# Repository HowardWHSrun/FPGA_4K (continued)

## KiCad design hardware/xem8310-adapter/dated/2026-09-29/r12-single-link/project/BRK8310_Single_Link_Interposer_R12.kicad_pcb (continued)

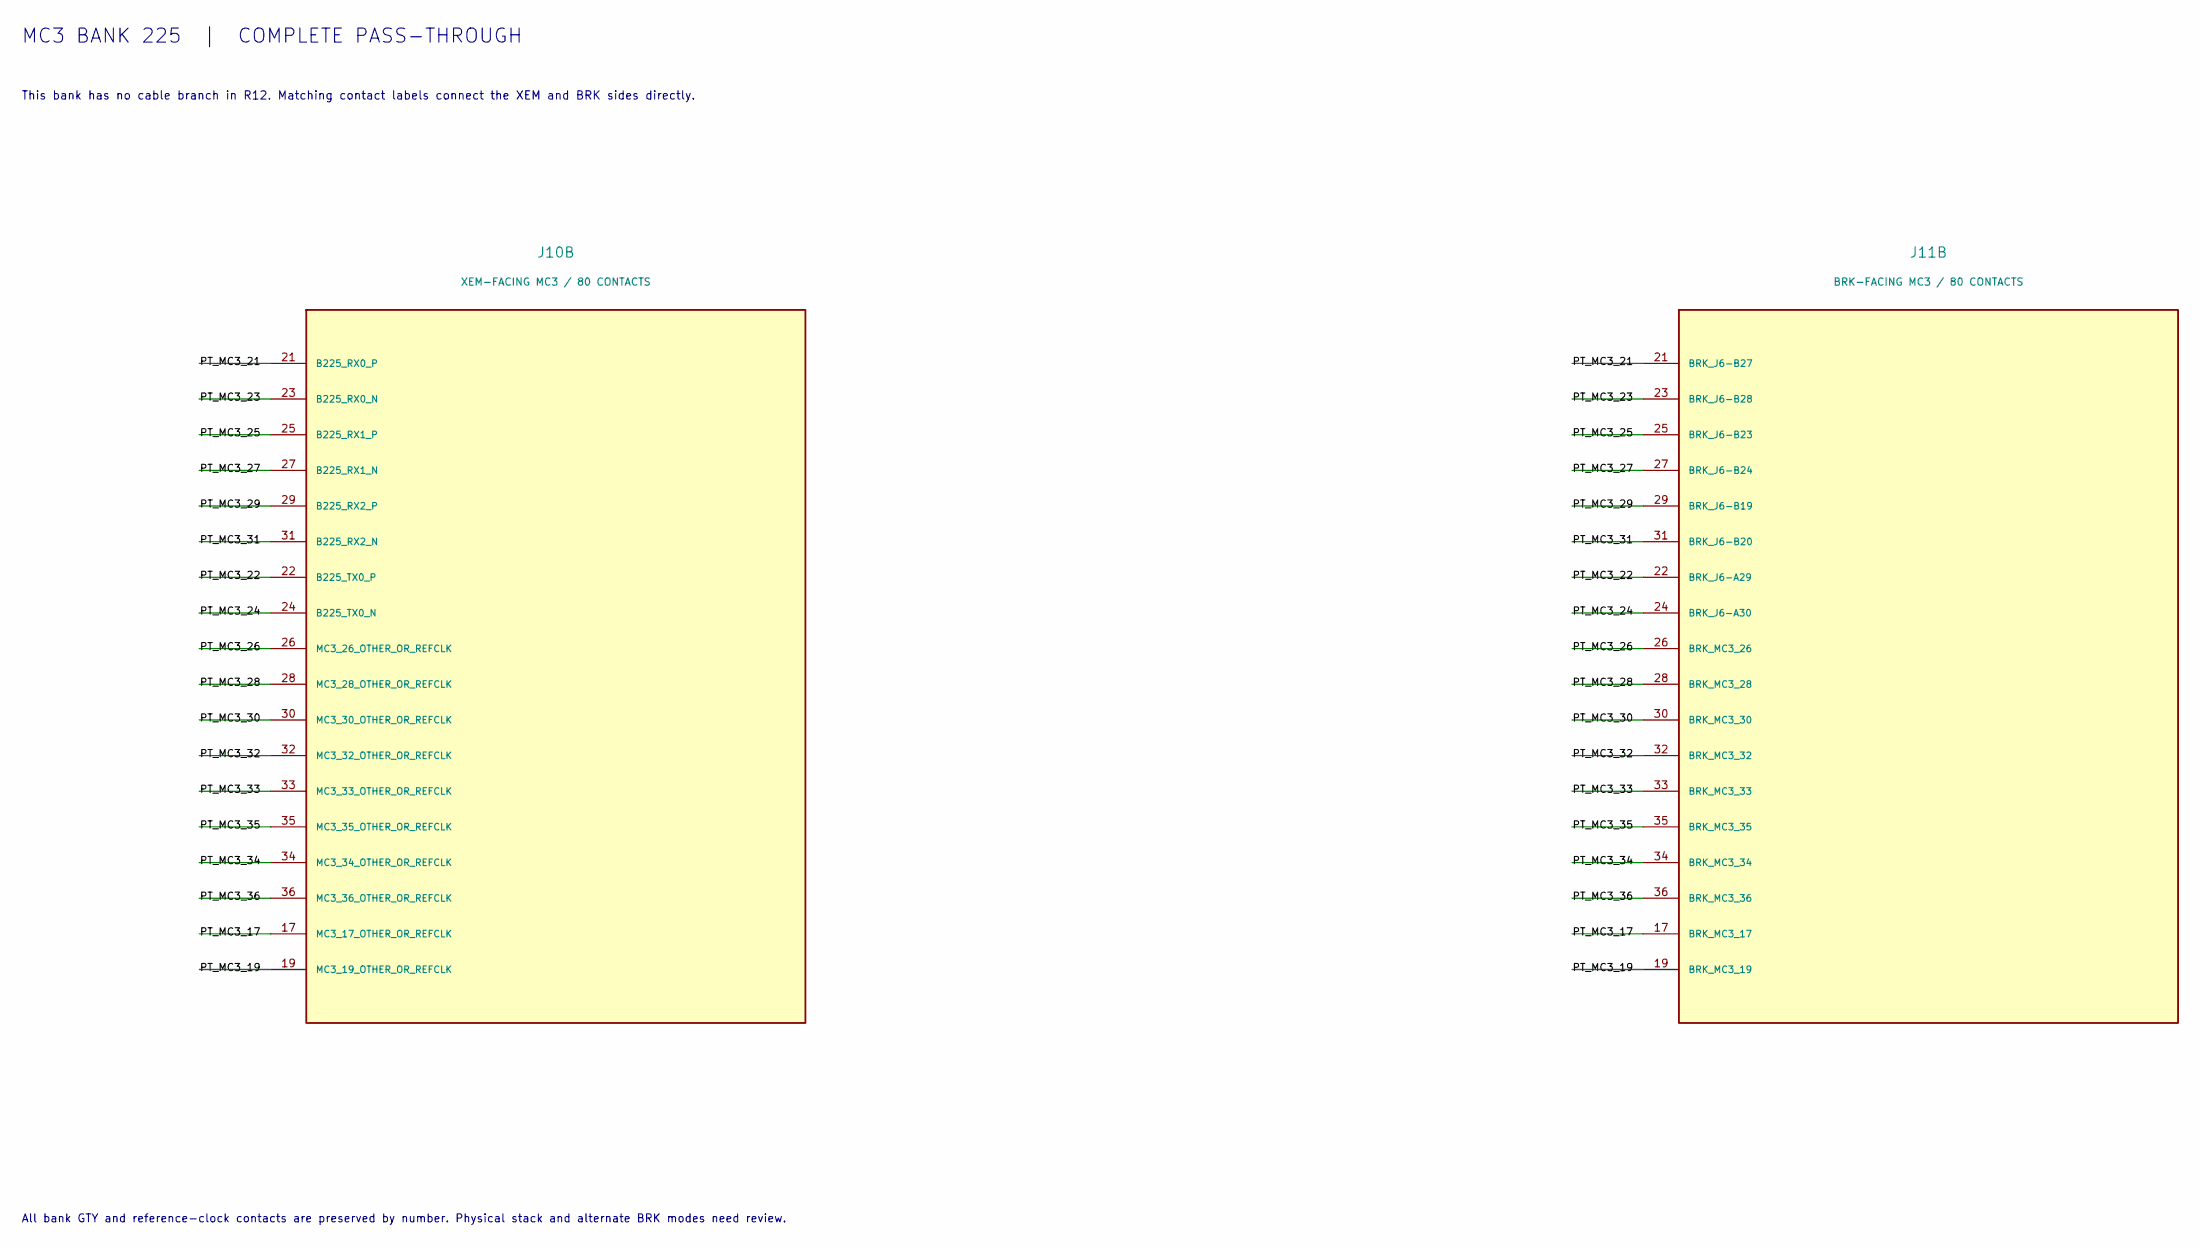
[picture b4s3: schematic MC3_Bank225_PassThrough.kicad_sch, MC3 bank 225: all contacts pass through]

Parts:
J10: XEM-FACING MC3 / 80 CONTACTS; QTH_040_01_Top_OpalKelly
J11: BRK-FACING MC3 / 80 CONTACTS; QSH_040_01_Bottom_SamtecDrawing

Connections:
/03 / MC3 BANK 225 - COMPLETE PASS-THROUGH/PT_MC3_17: J10.17 (MC3_17_OTHER_OR_REFCLK), J11.17 (BRK_MC3_17)
/03 / MC3 BANK 225 - COMPLETE PASS-THROUGH/PT_MC3_19: J10.19 (MC3_19_OTHER_OR_REFCLK), J11.19 (BRK_MC3_19)
/03 / MC3 BANK 225 - COMPLETE PASS-THROUGH/PT_MC3_21: J10.21 (B225_RX0_P), J11.21 (BRK_J6-B27)
/03 / MC3 BANK 225 - COMPLETE PASS-THROUGH/PT_MC3_22: J10.22 (B225_TX0_P), J11.22 (BRK_J6-A29)
/03 / MC3 BANK 225 - COMPLETE PASS-THROUGH/PT_MC3_23: J10.23 (B225_RX0_N), J11.23 (BRK_J6-B28)
/03 / MC3 BANK 225 - COMPLETE PASS-THROUGH/PT_MC3_24: J10.24 (B225_TX0_N), J11.24 (BRK_J6-A30)
/03 / MC3 BANK 225 - COMPLETE PASS-THROUGH/PT_MC3_25: J10.25 (B225_RX1_P), J11.25 (BRK_J6-B23)
/03 / MC3 BANK 225 - COMPLETE PASS-THROUGH/PT_MC3_26: J10.26 (MC3_26_OTHER_OR_REFCLK), J11.26 (BRK_MC3_26)
/03 / MC3 BANK 225 - COMPLETE PASS-THROUGH/PT_MC3_27: J10.27 (B225_RX1_N), J11.27 (BRK_J6-B24)
/03 / MC3 BANK 225 - COMPLETE PASS-THROUGH/PT_MC3_28: J10.28 (MC3_28_OTHER_OR_REFCLK), J11.28 (BRK_MC3_28)
/03 / MC3 BANK 225 - COMPLETE PASS-THROUGH/PT_MC3_29: J10.29 (B225_RX2_P), J11.29 (BRK_J6-B19)
/03 / MC3 BANK 225 - COMPLETE PASS-THROUGH/PT_MC3_30: J10.30 (MC3_30_OTHER_OR_REFCLK), J11.30 (BRK_MC3_30)
/03 / MC3 BANK 225 - COMPLETE PASS-THROUGH/PT_MC3_31: J10.31 (B225_RX2_N), J11.31 (BRK_J6-B20)
/03 / MC3 BANK 225 - COMPLETE PASS-THROUGH/PT_MC3_32: J10.32 (MC3_32_OTHER_OR_REFCLK), J11.32 (BRK_MC3_32)
/03 / MC3 BANK 225 - COMPLETE PASS-THROUGH/PT_MC3_33: J10.33 (MC3_33_OTHER_OR_REFCLK), J11.33 (BRK_MC3_33)
/03 / MC3 BANK 225 - COMPLETE PASS-THROUGH/PT_MC3_34: J10.34 (MC3_34_OTHER_OR_REFCLK), J11.34 (BRK_MC3_34)
/03 / MC3 BANK 225 - COMPLETE PASS-THROUGH/PT_MC3_35: J10.35 (MC3_35_OTHER_OR_REFCLK), J11.35 (BRK_MC3_35)
/03 / MC3 BANK 225 - COMPLETE PASS-THROUGH/PT_MC3_36: J10.36 (MC3_36_OTHER_OR_REFCLK), J11.36 (BRK_MC3_36)

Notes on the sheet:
MC3 BANK 225 | COMPLETE PASS-THROUGH
This bank has no cable branch in R12. Matching contact labels connect the XEM and BRK sides directly.
All bank GTY and reference-clock contacts are preserved by number. Physical stack and alternate BRK modes need review.

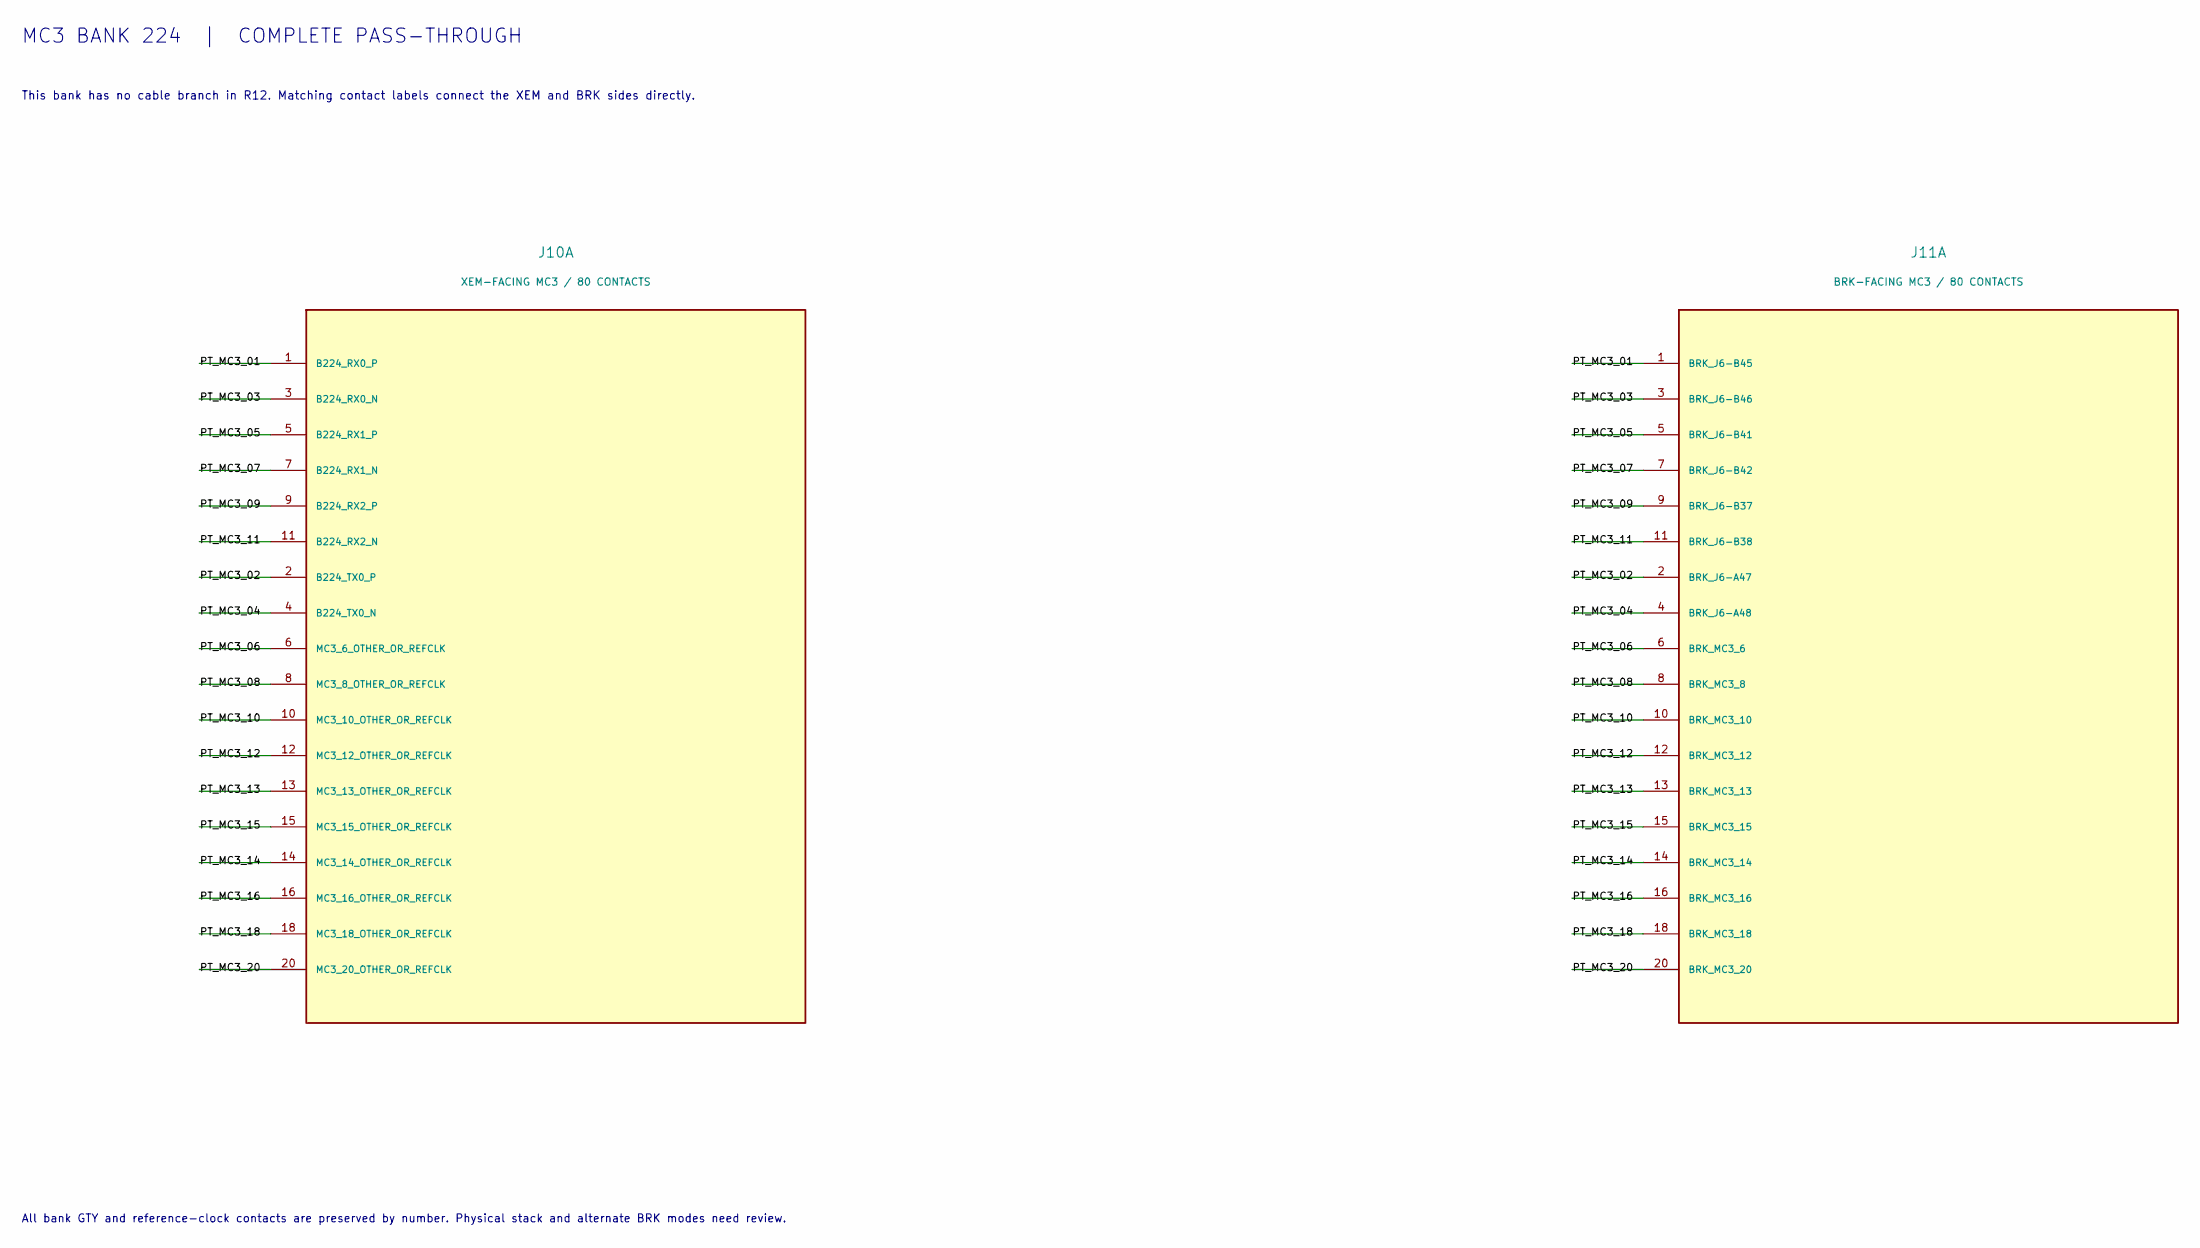
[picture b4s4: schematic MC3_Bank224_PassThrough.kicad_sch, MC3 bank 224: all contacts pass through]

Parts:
J10: XEM-FACING MC3 / 80 CONTACTS; QTH_040_01_Top_OpalKelly
J11: BRK-FACING MC3 / 80 CONTACTS; QSH_040_01_Bottom_SamtecDrawing

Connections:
/04 / MC3 BANK 224 - COMPLETE PASS-THROUGH/PT_MC3_01: J10.1 (B224_RX0_P), J11.1 (BRK_J6-B45)
/04 / MC3 BANK 224 - COMPLETE PASS-THROUGH/PT_MC3_02: J10.2 (B224_TX0_P), J11.2 (BRK_J6-A47)
/04 / MC3 BANK 224 - COMPLETE PASS-THROUGH/PT_MC3_03: J10.3 (B224_RX0_N), J11.3 (BRK_J6-B46)
/04 / MC3 BANK 224 - COMPLETE PASS-THROUGH/PT_MC3_04: J10.4 (B224_TX0_N), J11.4 (BRK_J6-A48)
/04 / MC3 BANK 224 - COMPLETE PASS-THROUGH/PT_MC3_05: J10.5 (B224_RX1_P), J11.5 (BRK_J6-B41)
/04 / MC3 BANK 224 - COMPLETE PASS-THROUGH/PT_MC3_06: J10.6 (MC3_6_OTHER_OR_REFCLK), J11.6 (BRK_MC3_6)
/04 / MC3 BANK 224 - COMPLETE PASS-THROUGH/PT_MC3_07: J10.7 (B224_RX1_N), J11.7 (BRK_J6-B42)
/04 / MC3 BANK 224 - COMPLETE PASS-THROUGH/PT_MC3_08: J10.8 (MC3_8_OTHER_OR_REFCLK), J11.8 (BRK_MC3_8)
/04 / MC3 BANK 224 - COMPLETE PASS-THROUGH/PT_MC3_09: J10.9 (B224_RX2_P), J11.9 (BRK_J6-B37)
/04 / MC3 BANK 224 - COMPLETE PASS-THROUGH/PT_MC3_10: J10.10 (MC3_10_OTHER_OR_REFCLK), J11.10 (BRK_MC3_10)
/04 / MC3 BANK 224 - COMPLETE PASS-THROUGH/PT_MC3_11: J10.11 (B224_RX2_N), J11.11 (BRK_J6-B38)
/04 / MC3 BANK 224 - COMPLETE PASS-THROUGH/PT_MC3_12: J10.12 (MC3_12_OTHER_OR_REFCLK), J11.12 (BRK_MC3_12)
/04 / MC3 BANK 224 - COMPLETE PASS-THROUGH/PT_MC3_13: J10.13 (MC3_13_OTHER_OR_REFCLK), J11.13 (BRK_MC3_13)
/04 / MC3 BANK 224 - COMPLETE PASS-THROUGH/PT_MC3_14: J10.14 (MC3_14_OTHER_OR_REFCLK), J11.14 (BRK_MC3_14)
/04 / MC3 BANK 224 - COMPLETE PASS-THROUGH/PT_MC3_15: J10.15 (MC3_15_OTHER_OR_REFCLK), J11.15 (BRK_MC3_15)
/04 / MC3 BANK 224 - COMPLETE PASS-THROUGH/PT_MC3_16: J10.16 (MC3_16_OTHER_OR_REFCLK), J11.16 (BRK_MC3_16)
/04 / MC3 BANK 224 - COMPLETE PASS-THROUGH/PT_MC3_18: J10.18 (MC3_18_OTHER_OR_REFCLK), J11.18 (BRK_MC3_18)
/04 / MC3 BANK 224 - COMPLETE PASS-THROUGH/PT_MC3_20: J10.20 (MC3_20_OTHER_OR_REFCLK), J11.20 (BRK_MC3_20)

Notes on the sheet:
MC3 BANK 224 | COMPLETE PASS-THROUGH
This bank has no cable branch in R12. Matching contact labels connect the XEM and BRK sides directly.
All bank GTY and reference-clock contacts are preserved by number. Physical stack and alternate BRK modes need review.

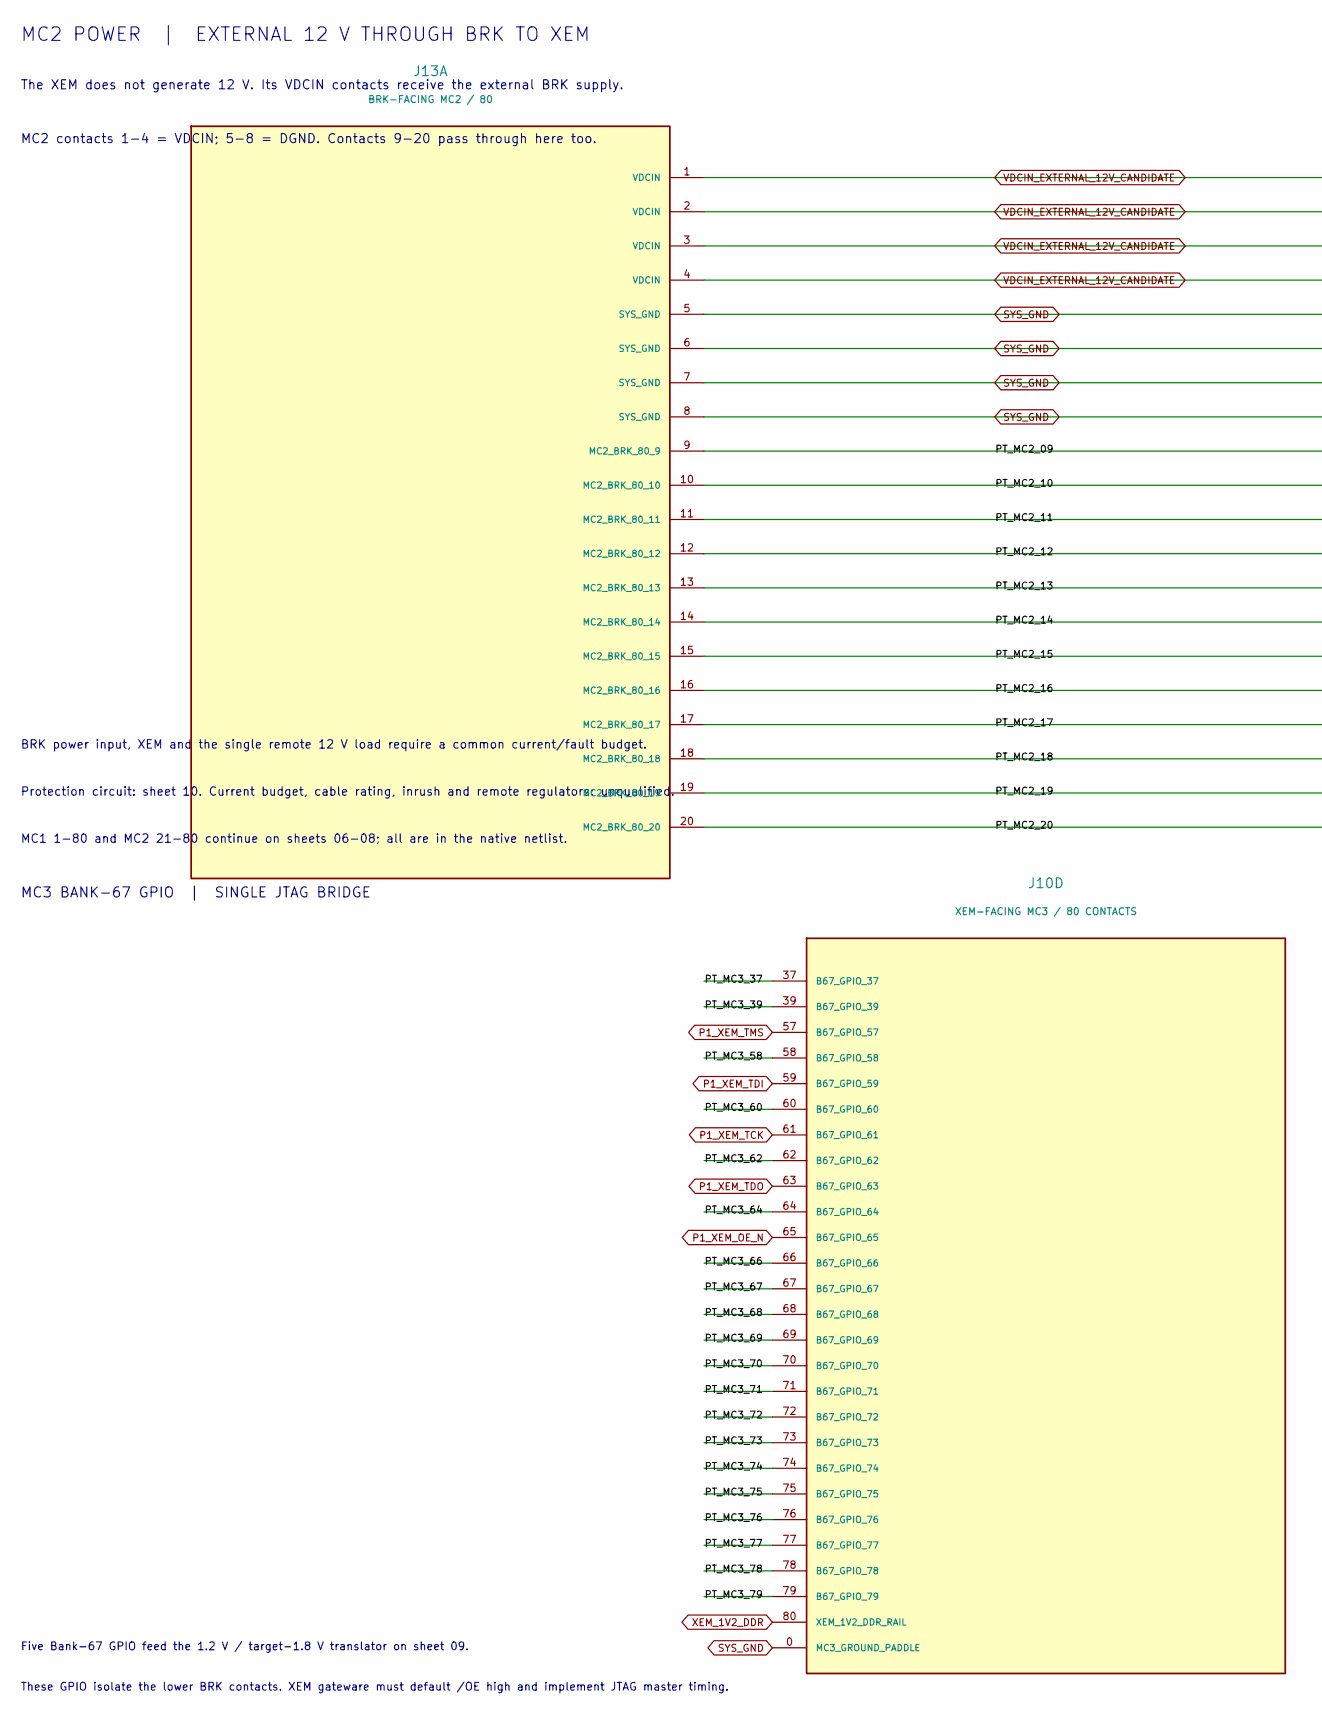
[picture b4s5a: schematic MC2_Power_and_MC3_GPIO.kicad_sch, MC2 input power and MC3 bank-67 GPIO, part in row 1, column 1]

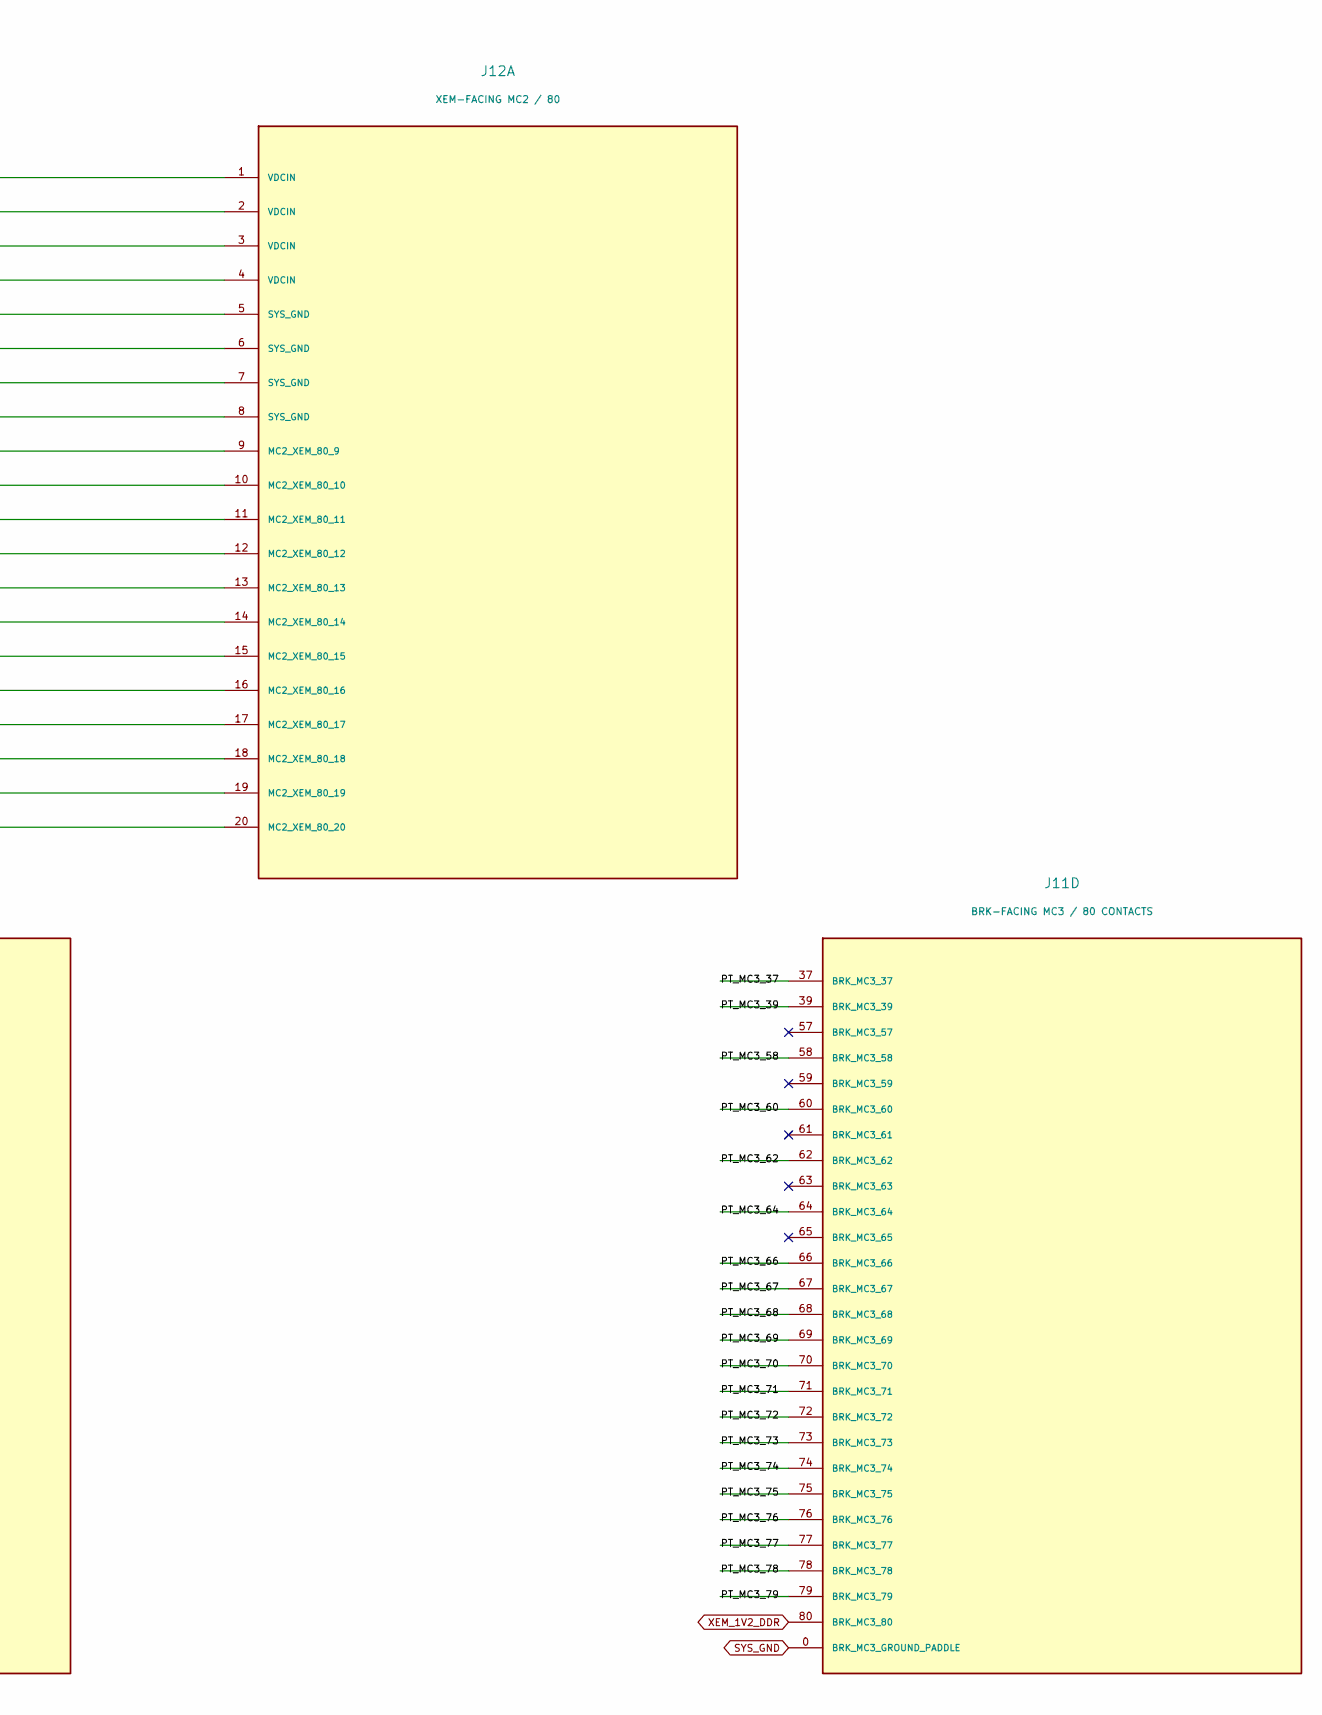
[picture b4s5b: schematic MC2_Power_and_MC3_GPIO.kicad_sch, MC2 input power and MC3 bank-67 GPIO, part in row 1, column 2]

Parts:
J10: XEM-FACING MC3 / 80 CONTACTS; QTH_040_01_Top_OpalKelly
J11: BRK-FACING MC3 / 80 CONTACTS; QSH_040_01_Bottom_SamtecDrawing
J12: XEM-FACING MC2 / 80; BTE_040_01_Top_OpalKelly
J13: BRK-FACING MC2 / 80; BSE_040_01_Bottom_SamtecDrawing

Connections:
/05 / MC2 POWER + MC3 BANK-67 GPIO/PT_MC2_09: J12.9 (MC2_XEM_80_9), J13.9 (MC2_BRK_80_9)
/05 / MC2 POWER + MC3 BANK-67 GPIO/PT_MC2_10: J12.10 (MC2_XEM_80_10), J13.10 (MC2_BRK_80_10)
/05 / MC2 POWER + MC3 BANK-67 GPIO/PT_MC2_11: J12.11 (MC2_XEM_80_11), J13.11 (MC2_BRK_80_11)
/05 / MC2 POWER + MC3 BANK-67 GPIO/PT_MC2_12: J12.12 (MC2_XEM_80_12), J13.12 (MC2_BRK_80_12)
/05 / MC2 POWER + MC3 BANK-67 GPIO/PT_MC2_13: J12.13 (MC2_XEM_80_13), J13.13 (MC2_BRK_80_13)
/05 / MC2 POWER + MC3 BANK-67 GPIO/PT_MC2_14: J12.14 (MC2_XEM_80_14), J13.14 (MC2_BRK_80_14)
/05 / MC2 POWER + MC3 BANK-67 GPIO/PT_MC2_15: J12.15 (MC2_XEM_80_15), J13.15 (MC2_BRK_80_15)
/05 / MC2 POWER + MC3 BANK-67 GPIO/PT_MC2_16: J12.16 (MC2_XEM_80_16), J13.16 (MC2_BRK_80_16)
/05 / MC2 POWER + MC3 BANK-67 GPIO/PT_MC2_17: J12.17 (MC2_XEM_80_17), J13.17 (MC2_BRK_80_17)
/05 / MC2 POWER + MC3 BANK-67 GPIO/PT_MC2_18: J12.18 (MC2_XEM_80_18), J13.18 (MC2_BRK_80_18)
/05 / MC2 POWER + MC3 BANK-67 GPIO/PT_MC2_19: J12.19 (MC2_XEM_80_19), J13.19 (MC2_BRK_80_19)
/05 / MC2 POWER + MC3 BANK-67 GPIO/PT_MC2_20: J12.20 (MC2_XEM_80_20), J13.20 (MC2_BRK_80_20)
/05 / MC2 POWER + MC3 BANK-67 GPIO/PT_MC3_37: J10.37 (B67_GPIO_37), J11.37 (BRK_MC3_37)
/05 / MC2 POWER + MC3 BANK-67 GPIO/PT_MC3_39: J10.39 (B67_GPIO_39), J11.39 (BRK_MC3_39)
/05 / MC2 POWER + MC3 BANK-67 GPIO/PT_MC3_58: J10.58 (B67_GPIO_58), J11.58 (BRK_MC3_58)
/05 / MC2 POWER + MC3 BANK-67 GPIO/PT_MC3_60: J10.60 (B67_GPIO_60), J11.60 (BRK_MC3_60)
/05 / MC2 POWER + MC3 BANK-67 GPIO/PT_MC3_62: J10.62 (B67_GPIO_62), J11.62 (BRK_MC3_62)
/05 / MC2 POWER + MC3 BANK-67 GPIO/PT_MC3_64: J10.64 (B67_GPIO_64), J11.64 (BRK_MC3_64)
/05 / MC2 POWER + MC3 BANK-67 GPIO/PT_MC3_66: J10.66 (B67_GPIO_66), J11.66 (BRK_MC3_66)
/05 / MC2 POWER + MC3 BANK-67 GPIO/PT_MC3_67: J10.67 (B67_GPIO_67), J11.67 (BRK_MC3_67)
/05 / MC2 POWER + MC3 BANK-67 GPIO/PT_MC3_68: J10.68 (B67_GPIO_68), J11.68 (BRK_MC3_68)
/05 / MC2 POWER + MC3 BANK-67 GPIO/PT_MC3_69: J10.69 (B67_GPIO_69), J11.69 (BRK_MC3_69)
/05 / MC2 POWER + MC3 BANK-67 GPIO/PT_MC3_70: J10.70 (B67_GPIO_70), J11.70 (BRK_MC3_70)
/05 / MC2 POWER + MC3 BANK-67 GPIO/PT_MC3_71: J10.71 (B67_GPIO_71), J11.71 (BRK_MC3_71)
/05 / MC2 POWER + MC3 BANK-67 GPIO/PT_MC3_72: J10.72 (B67_GPIO_72), J11.72 (BRK_MC3_72)
/05 / MC2 POWER + MC3 BANK-67 GPIO/PT_MC3_73: J10.73 (B67_GPIO_73), J11.73 (BRK_MC3_73)
/05 / MC2 POWER + MC3 BANK-67 GPIO/PT_MC3_74: J10.74 (B67_GPIO_74), J11.74 (BRK_MC3_74)
/05 / MC2 POWER + MC3 BANK-67 GPIO/PT_MC3_75: J10.75 (B67_GPIO_75), J11.75 (BRK_MC3_75)
/05 / MC2 POWER + MC3 BANK-67 GPIO/PT_MC3_76: J10.76 (B67_GPIO_76), J11.76 (BRK_MC3_76)
/05 / MC2 POWER + MC3 BANK-67 GPIO/PT_MC3_77: J10.77 (B67_GPIO_77), J11.77 (BRK_MC3_77)
/05 / MC2 POWER + MC3 BANK-67 GPIO/PT_MC3_78: J10.78 (B67_GPIO_78), J11.78 (BRK_MC3_78)
/05 / MC2 POWER + MC3 BANK-67 GPIO/PT_MC3_79: J10.79 (B67_GPIO_79), J11.79 (BRK_MC3_79)
P1_XEM_OE_N: J10.65 (B67_GPIO_65); also elsewhere on the board
P1_XEM_TCK: J10.61 (B67_GPIO_61); also elsewhere on the board
P1_XEM_TDI: J10.59 (B67_GPIO_59); also elsewhere on the board
P1_XEM_TDO: J10.63 (B67_GPIO_63); also elsewhere on the board
P1_XEM_TMS: J10.57 (B67_GPIO_57); also elsewhere on the board
SYS_GND: J10.0 (MC3_GROUND_PADDLE), J11.0 (BRK_MC3_GROUND_PADDLE), J12.5 (SYS_GND), J12.6 (SYS_GND), J12.7 (SYS_GND), J12.8 (SYS_GND), J13.5 (SYS_GND), J13.6 (SYS_GND), J13.7 (SYS_GND), J13.8 (SYS_GND); also elsewhere on the board
VDCIN_EXTERNAL_12V_CANDIDATE: J12.1 (VDCIN), J12.2 (VDCIN), J12.3 (VDCIN), J12.4 (VDCIN), J13.1 (VDCIN), J13.2 (VDCIN), J13.3 (VDCIN), J13.4 (VDCIN); also elsewhere on the board
XEM_1V2_DDR: J10.80 (XEM_1V2_DDR_RAIL), J11.80 (BRK_MC3_80); also elsewhere on the board

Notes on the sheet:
MC2 POWER | EXTERNAL 12 V THROUGH BRK TO XEM
The XEM does not generate 12 V. Its VDCIN contacts receive the external BRK supply.
MC2 contacts 1-4 = VDCIN; 5-8 = DGND. Contacts 9-20 pass through here too.
BRK power input, XEM and the single remote 12 V load require a common current/fault budget.
Protection circuit: sheet 10. Current budget, cable rating, inrush and remote regulators: unqualified.
MC1 1-80 and MC2 21-80 continue on sheets 06-08; all are in the native netlist.
MC3 BANK-67 GPIO | SINGLE JTAG BRIDGE
Five Bank-67 GPIO feed the 1.2 V / target-1.8 V translator on sheet 09.
These GPIO isolate the lower BRK contacts. XEM gateware must default /OE high and implement JTAG master timing.

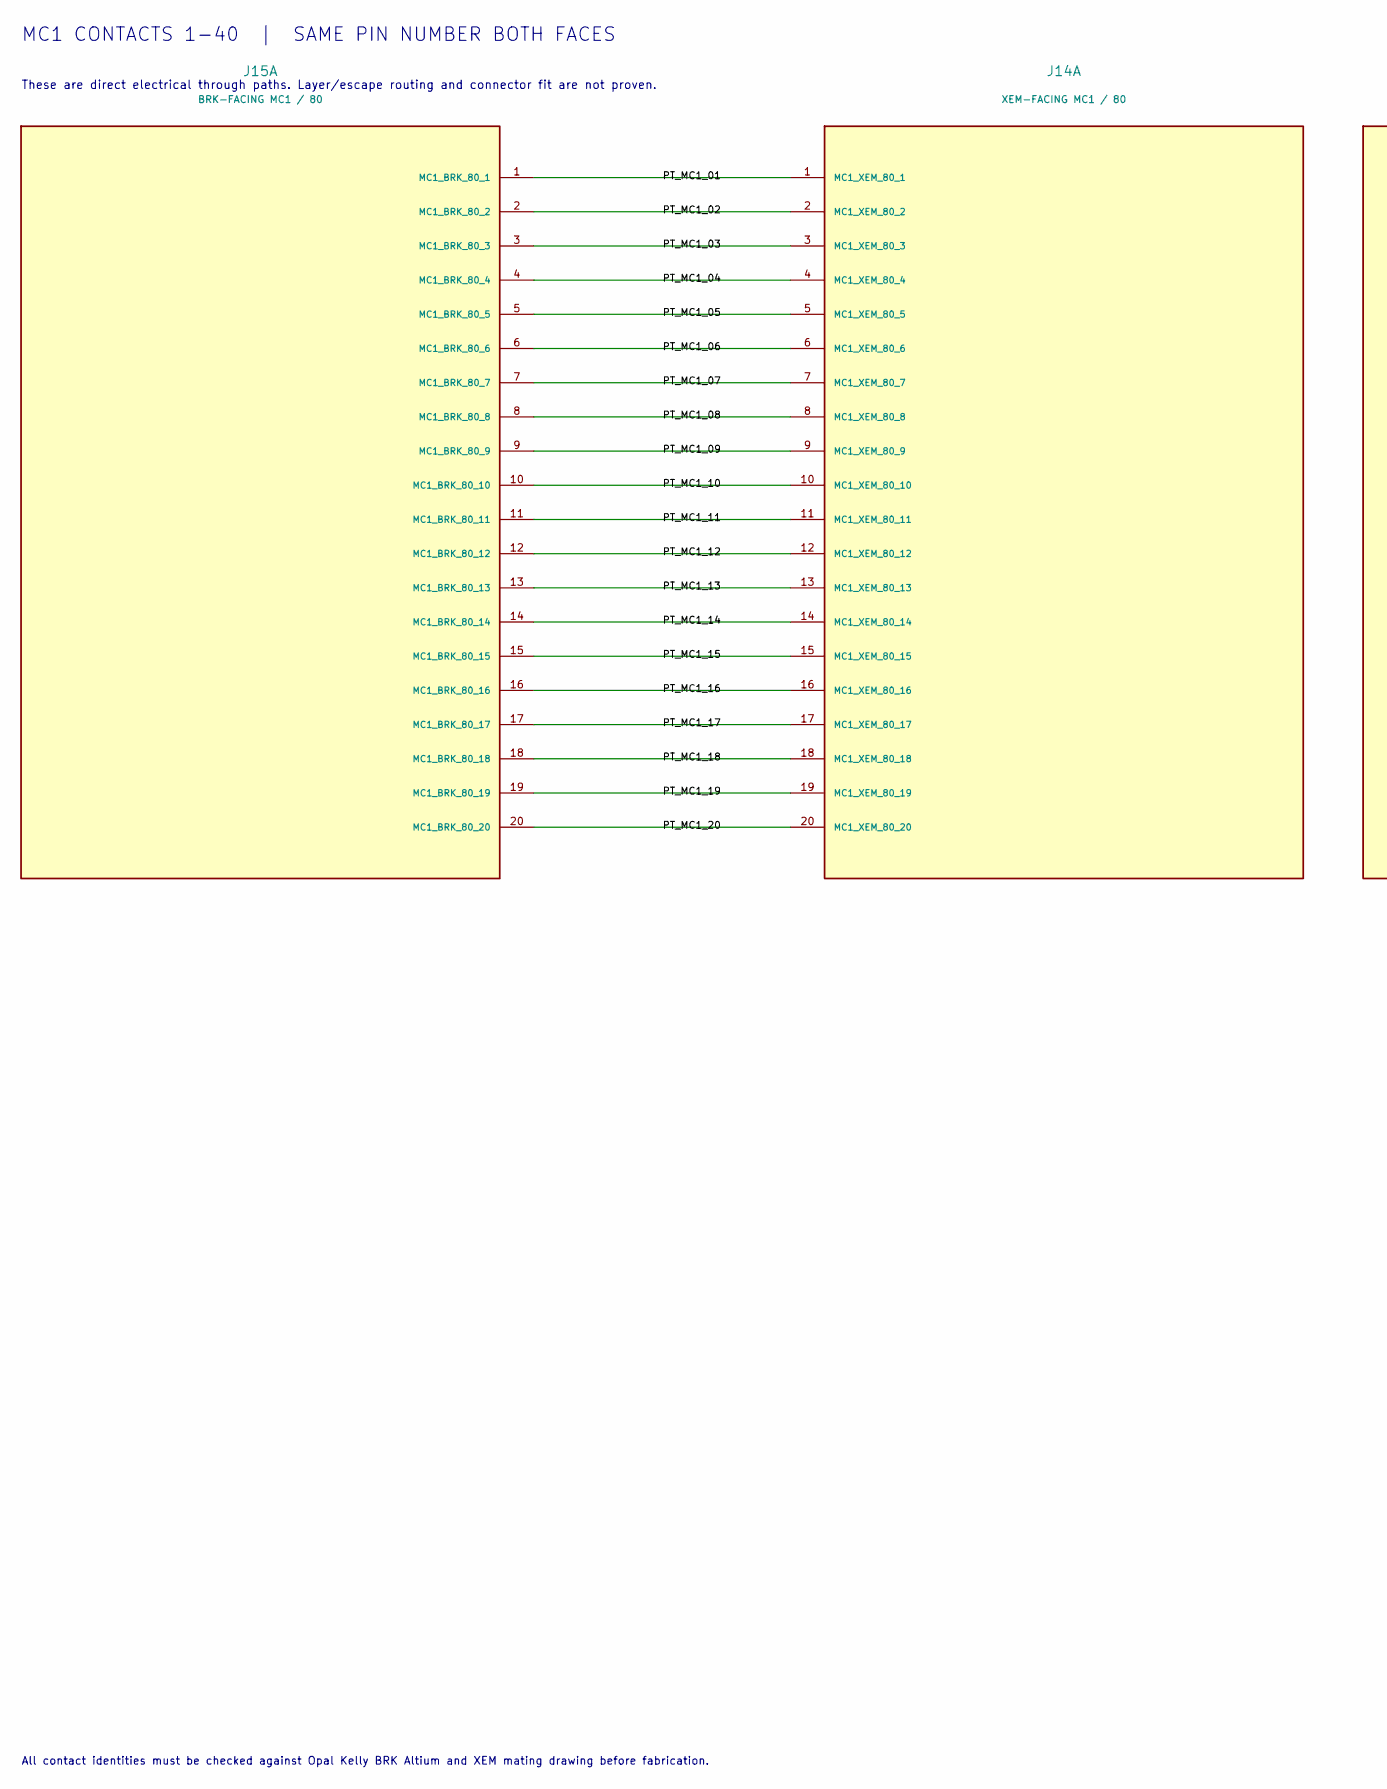
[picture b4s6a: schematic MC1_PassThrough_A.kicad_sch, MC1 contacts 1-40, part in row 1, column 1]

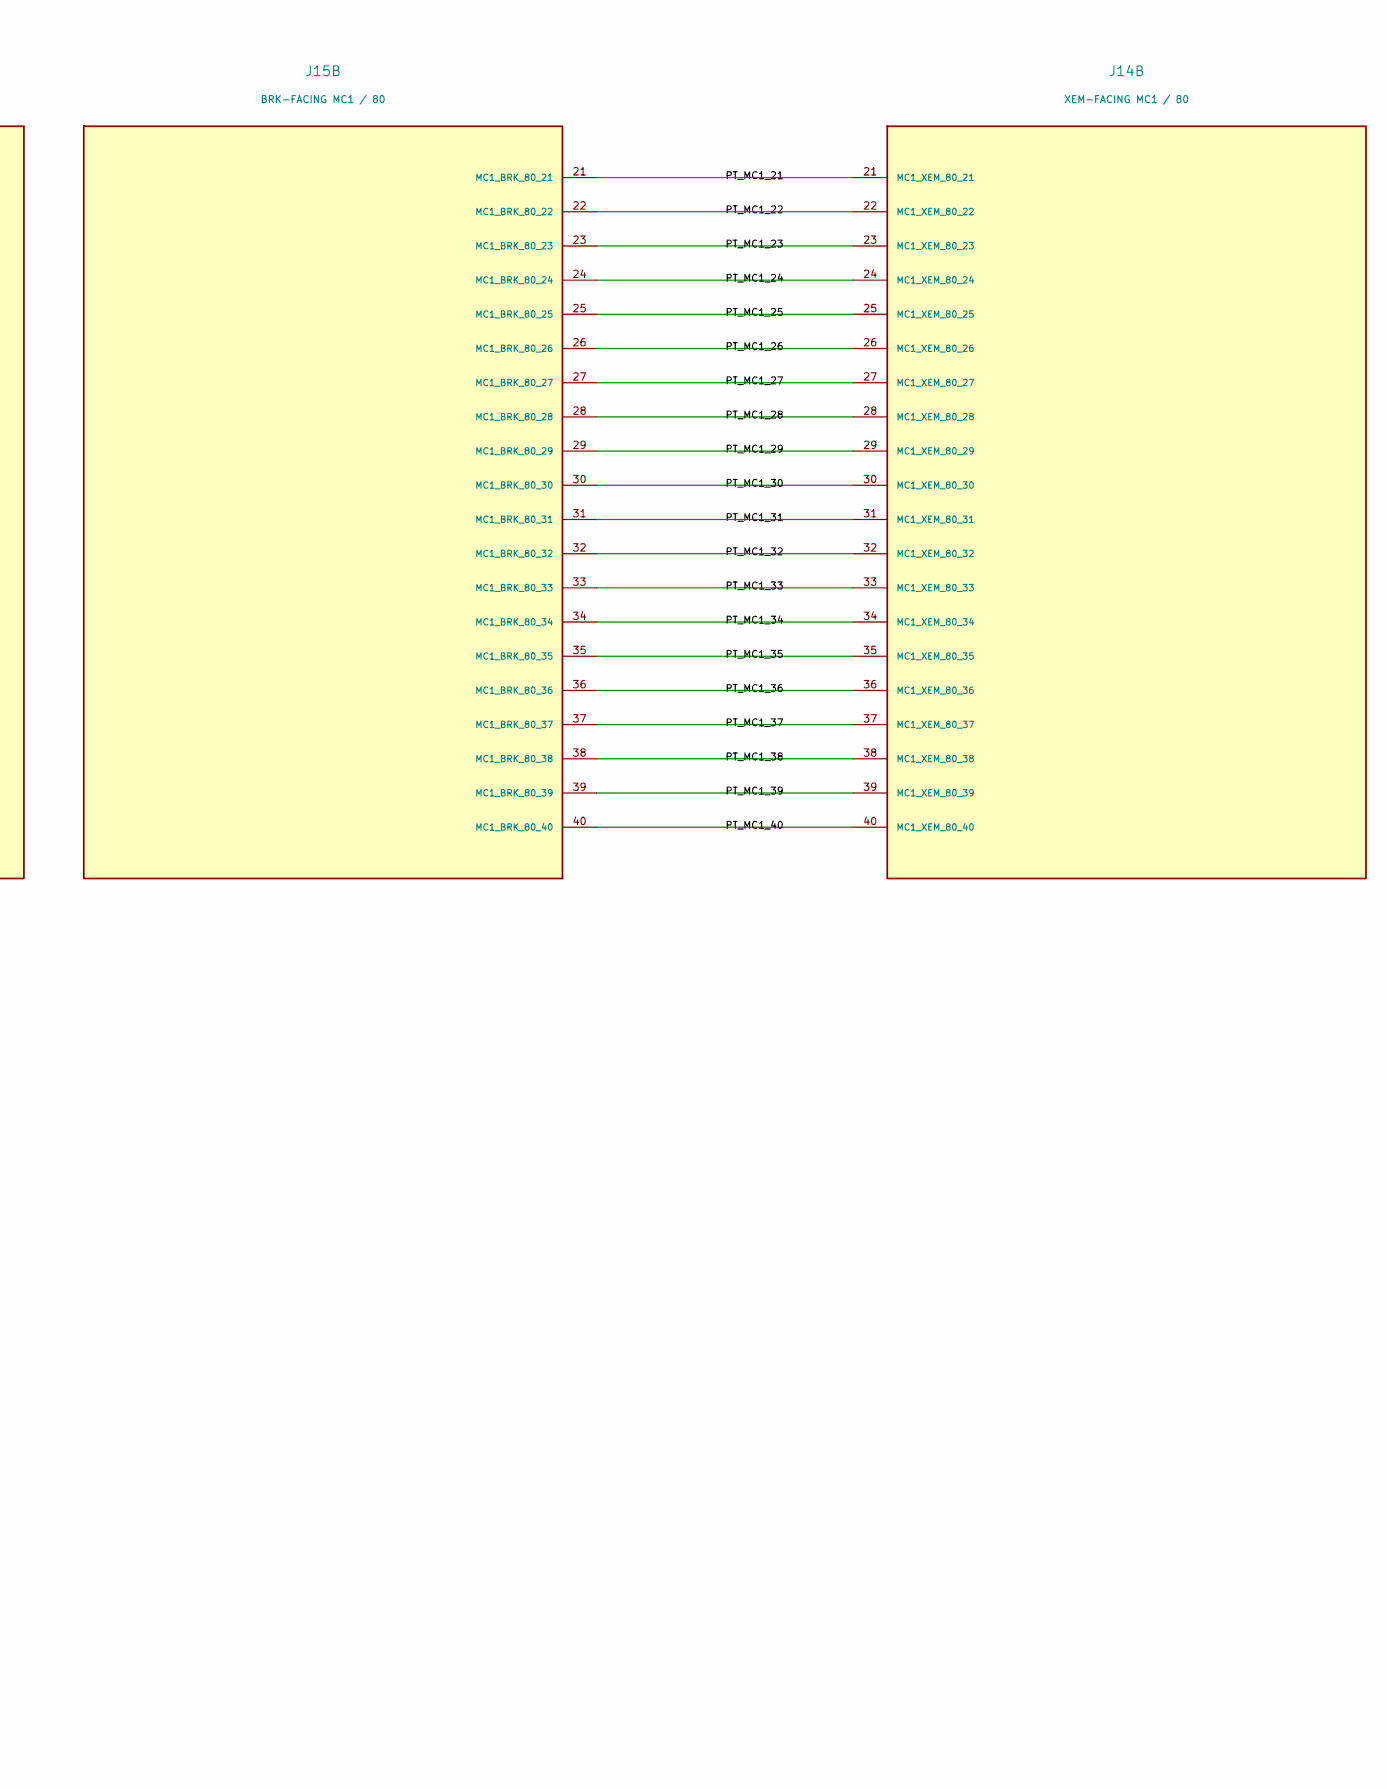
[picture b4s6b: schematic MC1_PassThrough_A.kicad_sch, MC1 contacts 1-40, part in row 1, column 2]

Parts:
J14: XEM-FACING MC1 / 80; BTE_040_01_Top_OpalKelly
J15: BRK-FACING MC1 / 80; BSE_040_01_Bottom_SamtecDrawing

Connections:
/06 / MC1 1-40 PASS-THROUGH/PT_MC1_01: J14.1 (MC1_XEM_80_1), J15.1 (MC1_BRK_80_1)
/06 / MC1 1-40 PASS-THROUGH/PT_MC1_02: J14.2 (MC1_XEM_80_2), J15.2 (MC1_BRK_80_2)
/06 / MC1 1-40 PASS-THROUGH/PT_MC1_03: J14.3 (MC1_XEM_80_3), J15.3 (MC1_BRK_80_3)
/06 / MC1 1-40 PASS-THROUGH/PT_MC1_04: J14.4 (MC1_XEM_80_4), J15.4 (MC1_BRK_80_4)
/06 / MC1 1-40 PASS-THROUGH/PT_MC1_05: J14.5 (MC1_XEM_80_5), J15.5 (MC1_BRK_80_5)
/06 / MC1 1-40 PASS-THROUGH/PT_MC1_06: J14.6 (MC1_XEM_80_6), J15.6 (MC1_BRK_80_6)
/06 / MC1 1-40 PASS-THROUGH/PT_MC1_07: J14.7 (MC1_XEM_80_7), J15.7 (MC1_BRK_80_7)
/06 / MC1 1-40 PASS-THROUGH/PT_MC1_08: J14.8 (MC1_XEM_80_8), J15.8 (MC1_BRK_80_8)
/06 / MC1 1-40 PASS-THROUGH/PT_MC1_09: J14.9 (MC1_XEM_80_9), J15.9 (MC1_BRK_80_9)
/06 / MC1 1-40 PASS-THROUGH/PT_MC1_10: J14.10 (MC1_XEM_80_10), J15.10 (MC1_BRK_80_10)
/06 / MC1 1-40 PASS-THROUGH/PT_MC1_11: J14.11 (MC1_XEM_80_11), J15.11 (MC1_BRK_80_11)
/06 / MC1 1-40 PASS-THROUGH/PT_MC1_12: J14.12 (MC1_XEM_80_12), J15.12 (MC1_BRK_80_12)
/06 / MC1 1-40 PASS-THROUGH/PT_MC1_13: J14.13 (MC1_XEM_80_13), J15.13 (MC1_BRK_80_13)
/06 / MC1 1-40 PASS-THROUGH/PT_MC1_14: J14.14 (MC1_XEM_80_14), J15.14 (MC1_BRK_80_14)
/06 / MC1 1-40 PASS-THROUGH/PT_MC1_15: J14.15 (MC1_XEM_80_15), J15.15 (MC1_BRK_80_15)
/06 / MC1 1-40 PASS-THROUGH/PT_MC1_16: J14.16 (MC1_XEM_80_16), J15.16 (MC1_BRK_80_16)
/06 / MC1 1-40 PASS-THROUGH/PT_MC1_17: J14.17 (MC1_XEM_80_17), J15.17 (MC1_BRK_80_17)
/06 / MC1 1-40 PASS-THROUGH/PT_MC1_18: J14.18 (MC1_XEM_80_18), J15.18 (MC1_BRK_80_18)
/06 / MC1 1-40 PASS-THROUGH/PT_MC1_19: J14.19 (MC1_XEM_80_19), J15.19 (MC1_BRK_80_19)
/06 / MC1 1-40 PASS-THROUGH/PT_MC1_20: J14.20 (MC1_XEM_80_20), J15.20 (MC1_BRK_80_20)
/06 / MC1 1-40 PASS-THROUGH/PT_MC1_21: J14.21 (MC1_XEM_80_21), J15.21 (MC1_BRK_80_21)
/06 / MC1 1-40 PASS-THROUGH/PT_MC1_22: J14.22 (MC1_XEM_80_22), J15.22 (MC1_BRK_80_22)
/06 / MC1 1-40 PASS-THROUGH/PT_MC1_23: J14.23 (MC1_XEM_80_23), J15.23 (MC1_BRK_80_23)
/06 / MC1 1-40 PASS-THROUGH/PT_MC1_24: J14.24 (MC1_XEM_80_24), J15.24 (MC1_BRK_80_24)
/06 / MC1 1-40 PASS-THROUGH/PT_MC1_25: J14.25 (MC1_XEM_80_25), J15.25 (MC1_BRK_80_25)
/06 / MC1 1-40 PASS-THROUGH/PT_MC1_26: J14.26 (MC1_XEM_80_26), J15.26 (MC1_BRK_80_26)
/06 / MC1 1-40 PASS-THROUGH/PT_MC1_27: J14.27 (MC1_XEM_80_27), J15.27 (MC1_BRK_80_27)
/06 / MC1 1-40 PASS-THROUGH/PT_MC1_28: J14.28 (MC1_XEM_80_28), J15.28 (MC1_BRK_80_28)
/06 / MC1 1-40 PASS-THROUGH/PT_MC1_29: J14.29 (MC1_XEM_80_29), J15.29 (MC1_BRK_80_29)
/06 / MC1 1-40 PASS-THROUGH/PT_MC1_30: J14.30 (MC1_XEM_80_30), J15.30 (MC1_BRK_80_30)
/06 / MC1 1-40 PASS-THROUGH/PT_MC1_31: J14.31 (MC1_XEM_80_31), J15.31 (MC1_BRK_80_31)
/06 / MC1 1-40 PASS-THROUGH/PT_MC1_32: J14.32 (MC1_XEM_80_32), J15.32 (MC1_BRK_80_32)
/06 / MC1 1-40 PASS-THROUGH/PT_MC1_33: J14.33 (MC1_XEM_80_33), J15.33 (MC1_BRK_80_33)
/06 / MC1 1-40 PASS-THROUGH/PT_MC1_34: J14.34 (MC1_XEM_80_34), J15.34 (MC1_BRK_80_34)
/06 / MC1 1-40 PASS-THROUGH/PT_MC1_35: J14.35 (MC1_XEM_80_35), J15.35 (MC1_BRK_80_35)
/06 / MC1 1-40 PASS-THROUGH/PT_MC1_36: J14.36 (MC1_XEM_80_36), J15.36 (MC1_BRK_80_36)
/06 / MC1 1-40 PASS-THROUGH/PT_MC1_37: J14.37 (MC1_XEM_80_37), J15.37 (MC1_BRK_80_37)
/06 / MC1 1-40 PASS-THROUGH/PT_MC1_38: J14.38 (MC1_XEM_80_38), J15.38 (MC1_BRK_80_38)
/06 / MC1 1-40 PASS-THROUGH/PT_MC1_39: J14.39 (MC1_XEM_80_39), J15.39 (MC1_BRK_80_39)
/06 / MC1 1-40 PASS-THROUGH/PT_MC1_40: J14.40 (MC1_XEM_80_40), J15.40 (MC1_BRK_80_40)

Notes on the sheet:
MC1 CONTACTS 1-40 | SAME PIN NUMBER BOTH FACES
These are direct electrical through paths. Layer/escape routing and connector fit are not proven.
All contact identities must be checked against Opal Kelly BRK Altium and XEM mating drawing before fabrication.
